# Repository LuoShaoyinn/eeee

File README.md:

# ESP32 Robot Controller

Four-wheel JGA25-2430-CE production controller for the carrier board. It uses active-low 20 kHz PWM, each motor's direction line, and the yellow FG speed output.

| Wheel | PWM | Direction | FG |
|---|---:|---:|---:|
| M1/front-left | GPIO23 | GPIO32 | GPIO36 |
| M2/front-right | GPIO21 | GPIO25 | GPIO39 |
| M3/rear-left | GPIO26 | GPIO27 | GPIO35 |
| M4/rear-right | GPIO19 | GPIO13 | GPIO34 |

The carrier supplies the required 3.3 V pull-ups for FG. FG is single-channel speed magnitude, not quadrature: it cannot prove direction. The firmware uses it for PI speed feedback and zero-speed confirmation before reversal; commanded DIR supplies the sign. Parameters are 18 FG pulses/output revolution, 620 RPM no-load, and 450 RPM rated-load. The wheel controller runs every 20 ms and updates its PCNT-derived RPM/PID feedback every 60 ms. The controller starts stopped, ramps duty, and stops after 500 ms without a valid command.

Chassis values: 190 mm wheel-center square and 23 mm wheel radius. The mirrored right-side mounts use inverted electrical direction by default (M2 and M4). Validate each wheel one at a time and correct `invert_direction` in `main/motor_control_main.c` for the actual Mecanum roller handedness/wiring. The FG source emits 9 pulses per motor-shaft revolution and the 9.6:1 gearbox yields 86.4 FG edges per output-shaft revolution. `encoder_pulses_per_output_rev` accepts fractional values for this reason.

`ROBOT_ENABLE_WIFI` in `main/motor_control_main.c` is `0` by default, so the
robot starts with its Wi-Fi radio and UDP listener disabled. The Cubie UART0
link is therefore the sole runtime control interface. Set the switch to `1`
to restore the retained AP/station and UDP control path; then copy
`main/wifi_credentials.h.example` to ignored local `main/wifi_credentials.h`.
An ESP32-WROOM-32 supports 2.4 GHz Wi-Fi only.

```sh
source /opt/esp-idf/export.sh
idf.py build
idf.py -p /dev/ttyUSB0 flash monitor
```

With the host connected to the ESP32 fallback AP:

```sh
python3 tools/keyboard_drive.py --host 192.168.4.1
```

UDP port `3333` accepts `drive FORWARD STRAFE TURN` with values from `-1.0` to `1.0`, `wheel MOTOR SPEED`, `stop`, `telemetry`, or `pid [KP KI]`. The PID query returns active gains; setting gains resets integrators immediately. The telemetry response contains per-wheel target, PCNT-derived RPM, latest FG edges, cumulative PCNT edges, duty, and reversal state. Subtract two `total` readings over a known interval to inspect hardware-counter edge rate directly.

Drive changes use a bounded PWM ramp. A regular `stop` coasts down at the configured deceleration rate. A direction reversal first ramps PWM to zero, waits for the FG signal to become quiet and observes the reversal dwell, then changes the direction line. A lost UDP command stream remains an immediate coast-to-stop safety action.

Minimal ESP-IDF application for an ESP32. The application prints `Hello, ESP32!` once per second over the default console UART.

## Hardware

The connected device was detected as:

- Chip: ESP32-D0WDQ6
- Revision: v1.1
- Features: Wi-Fi, Bluetooth, dual core
- Flash: 4 MB
- USB-UART port: `/dev/ttyUSB0`

The USB-UART bridge is a WCH CH340 (`1a86:7523`).

## Remote IMU debug

The carrier board's `J30` IMU header uses I2C. Connect JY61P `VCC` to `3V3`,
`GND` to `GND`, `SCL` to ESP32 `GPIO5`, and `SDA` to ESP32 `GPIO33`.
The firmware reads the module's default I2C address `0x50` at 100 kHz. Do not
also connect the JY61P UART pins for this integration.

From any device on the ESP32 Wi-Fi network, send UDP `imu` to port `3333`.
The reply reports the latest acceleration, angular rate, roll/pitch/yaw, frame
count, transaction-error count, and data age. A reply of `waiting for JY61P
I2C addr 0x50` indicates a wiring, supply, pull-up, or address/mode problem.

## S3 remote debug

S3 is a standard positional MG995 on GPIO17. At boot and after `stop`, PWM is
disabled, so a reset cannot move or hold a blocked linkage.
`s3 ANGLE` commands a slow one-degree-per-50-ms move over 0-180 degrees;
`s3 center` commands 60 degrees. `s3 release` stops PWM and releases holding
torque immediately. The MG995 has no angle readback: remove or align the horn
with the linkage at the intended center while unpowered before the first
installed test.

Send `s3` without an argument to inspect the commanded state. The reply shows
the most recently applied angle, target angle, 1,550-2,125 us pulse width,
50 Hz duty percentage, and the exact 16-bit LEDC duty count. After `s3
release`, the reported output duty is zero even though the last commanded angle
is retained for reference.

For unloaded endpoint calibration only, `s3 pulse PULSE_US` bypasses the angle
map and applies an immediate 1550-2125 us pulse at 50 Hz. Increase it in small
steps above 2000 us, and issue `s3 release` immediately if the servo buzzes,
heats, or reaches a hard stop. This command does not imply an angle.

Run `python3 tools/keyboard_drive.py --s3` on the host for a guarded manual
test: `A`/`D` adjust in 5-degree steps, `0` commands 0 degrees, `C` commands
60 degrees, and Space or Escape releases the servo.

Watch IMU telemetry over Wi-Fi with `python3 tools/keyboard_drive.py --imu`;
it keeps retrying until stopped with Ctrl-C, so it can be started before the
ESP32 powers on.

## Cubie UART debug and control

The carrier `JPI1` UART is ESP32 UART0 at 115200 baud, 8N1, with the 470 ohm
series resistors already fitted. Its connection is crossed: carrier
`PI_UART_TX_3V3` goes to Cubie RXD; carrier `PI_UART_RX_3V3` goes to Cubie TXD;
grounds join. Do not connect either 5 V or 3.3 V supply between boards.

Send one ASCII command per newline. UART accepts all production controls:
`state`, `imu`, `telemetry`, `drive F S T`, `twist VX_MPS VY_MPS WZ_RADPS`,
`wheel M SPEED`, `raw M DUTY`, `pid [KP KI]`, `s3 ANGLE`, `s3 center`,
`s3 release`, `ga25 DUTY`, and `stop`. Each command reply starts with `@ `.
For example, send `imu\n` to read the latest IMU data, or `s3 60\n` to move
S3 slowly to center. `s3 release\n` and `stop\n` release S3 immediately.

`state` is the compact control-loop snapshot: timestamp, IMU age/gyro/angle,
four wheel RPM/FG samples, and GA25 state. `twist` is the Cubie physical-unit
body command. It is conservatively limited to `+/-1.00 m/s` forward/strafe and
`+/-2.00 rad/s` yaw pending chassis calibration. The legacy normalized `drive`
command remains for bench tests.

Each chassis wheel has a hardware-PCNT speed PID loop. Startup ramps at 2.5%
duty per 20 ms to overcome static friction without an abrupt full-duty step.
When at least two wheels have valid encoder samples, a cross-wheel guard limits
any wheel running more than 10% ahead of the slowest commanded wheel ratio; the
lagging wheel retains its original PID target to recover. `telemetry` reports
this as `sync ACTIVE REFERENCE_RPM`.

The [Cubie C++ transport](cubie-robot/README.md) owns `/dev/ttyAS2` through
the enabled `robotd.service`. Its `robotctl` client communicates through a
local Unix socket rather than opening the serial port directly. `robotd`
refreshes active twists at 25 Hz, stops after 250 ms without client refreshes,
and relies on the ESP32's independent 500 ms watchdog as the second stop layer.

`raw M DUTY` is a single-JGA25 wheel wiring test which bypasses PCNT/encoder feedback
and PID. `M` is connector 1 through 4 and `DUTY` is -100 through 100. Refresh
the command within 500 ms while it should run; otherwise the firmware stops it.

The separate 6 V GA25-370 driving motor is controlled through the external
L298N, not `raw M DUTY`. Keep the L298N `ENA` jumper fitted. On the carrier's
`J40` header, GPIO12 (physical pin 3, 10 kOhm pulldown) drives L298N `IN1` and
GPIO16 (physical pin 1, 10 kOhm pulldown) drives L298N `IN2`. GPIO14 (physical
pin 2, no pulldown) is the single-channel GA25 encoder input. The PCB's old
`ENA`/`IN1`/`IN2` silkscreen labels therefore describe the physical traces, not
the new external L298N connection order. Never connect J40 pin 1 to L298N
`ENA`, and do not remove the L298N `ENA` jumper. The encoder must be a 3.3 V
safe signal before it reaches GPIO14.

Use `ga25 DUTY` for signed open-loop PWM. `ga25` reports the latest hardware
counter sample and cumulative encoder edges; no GA25 encoder PID is enabled
until its pulses-per-output-revolution is measured. Run `python3 tools/keyboard_drive.py --ga25 --host
192.168.19.137` for an interactive test; A/D change PWM by 5%, and Space/Esc
ramps to a stop.

### GA25 bench result

The external L298N and GA25-370 were verified with the above reassigned wiring.
Positive `ga25` duty produces a 20 kHz PWM waveform at the L298N motor output;
the motor-side average voltage is duty-scaled and includes the L298N bridge
drop, so it is lower than the 5 V supply. At 25% duty the measured average was
about 0.6 V, which was insufficient to reliably overcome static friction. The
motor started consistently at 80% duty.

The encoder on GPIO14 was counted by ESP32 PCNT hardware with a 10 us glitch
filter. With the mechanism free, five-second count windows measured:

| Command duty | Encoder edges | Window | Edge rate |
|---:|---:|---:|---:|
| 60% | 1,545 | 5.37 s | 288 edges/s |
| 80% | 2,633 | 5.34 s | 493 edges/s |

This confirms the encoder signal and the count rate scale with motor command.
It does not establish output RPM: measure encoder pulses per output revolution
before converting these counts into speed or enabling closed-loop GA25 control.
Always issue `ga25 0` or `stop` after a bench run; the command watchdog also
ramps GA25 to zero after 500 ms without refreshes.

### Collector recovery loop

The GA25 collector is disabled at ESP32 boot. `collector start` enables a
firmware-owned loop: it drives the collector reverse at 90%; if the GPIO14
encoder reports no edge for two seconds, it releases the L298N for 1.2 seconds,
then drives forward at 20% for exactly two output-shaft revolutions before
returning to reverse. This loop repeats until `collector stop`, `stop`, a
manual `ga25` command, or OTA update. A forward-clear phase taking more than
30 seconds enters a released `fault` state.

Before the first start, measure GPIO14 edges over a known number of output
shaft rotations and save the resulting edges-per-output-revolution value:

```sh
collector ppr EDGES_PER_OUTPUT_REV
collector start
collector
collector stop
```

The value is stored in ESP32 NVS and survives reboot. Without it, `collector
start` still runs reverse collection at 90%, but after a two-second stall it
releases and enters `fault`; it never estimates shaft revolutions from motor
time. Positive `ga25` duty is forward (`IN1` PWM) and negative duty is reverse
(`IN2` PWM).

## UART application updates

`partitions.csv` reserves two 1.875 MiB application slots. This enables updates
over the existing Cubie UART link after a one-time manual migration. The ESP32
ROM downloader cannot be entered from application code on this DevKit because
GPIO0 is only sampled during reset.

For the one-time migration, put the ESP32 in download mode with the physical
BOOT/EN buttons and flash the bootloader, partition table, and application in
one operation. Subsequent updates need no button press:

```sh
python3 tools/uart_ota_update.py build/esp32_hello_world.bin --port /dev/ttyAS2
```

The updater sends `ota SIZE CRC32` over UART0, writes the inactive slot, checks
the transferred image CRC32, marks that slot for the next boot, and reboots.
It stops the chassis, releases S3, and stops GA25 before accepting an image.
CRC32 protects against accidental serial corruption; it is not a signed or
authenticated update format, so only run the updater from the trusted Cubie.

## Environment

This project was built with ESP-IDF v6.0.2 on Arch Linux. Load the ESP-IDF toolchain before using `idf.py`:

```bash
source /opt/esp-idf/export.sh
```

## Build

Configure the target and build:

```bash
idf.py set-target esp32
idf.py build
```

The application binary is generated at `build/esp32_hello_world.bin`.

## Flash and monitor

Flash the connected board:

```bash
idf.py -p /dev/ttyUSB0 flash
```

Open the serial monitor at 115200 baud:

```bash
idf.py -p /dev/ttyUSB0 monitor
```

The monitor should show repeated `Hello, ESP32!` lines. Press `Ctrl-]` to exit.

## Project layout

- `CMakeLists.txt`: ESP-IDF project definition
- `main/hello_world_main.c`: application entry point
- `main/CMakeLists.txt`: component registration
- `sdkconfig.defaults`: shared default configuration
- `.gitignore`: generated ESP-IDF output exclusions

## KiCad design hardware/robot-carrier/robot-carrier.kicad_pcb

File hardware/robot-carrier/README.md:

# ESP32-WROOM-32 / Raspberry Pi 4B carrier board

This directory contains the first KiCad carrier-board sample for the mobile
robot. It is a placement and interface prototype, not yet a manufacturing
release. Power routing, thermal validation, and exact mechanical dimensions
must be reviewed before ordering a PCB.

## Project files

- `robot-carrier.kicad_pcb`: routed 60 mm x 73.5 mm two-sided board.
- `robot-carrier.kicad_sch`: authoritative electrical schematic.
- `robot-carrier.kicad_dru`: minimum widths for any added 5 V or battery tracks.
- `robot-carrier.kicad_pro`: KiCad project metadata.
- `RobotCarrier.kicad_sym`, `Custom.pretty/`, `sym-lib-table`, and
  `fp-lib-table`: project-local symbols and footprints.
- `carrier-architecture.md`: power tree, pin map, connector pinouts, and bring-up notes.
- `lcsc-selected-parts.md`: selected purchasable LCSC parts and remaining
  safety-critical sourcing decisions.

The board keeps the ESP32 DevKit on the carrier. The Raspberry Pi 4B is
physically separate and connects through `JPI1` using a jumper harness for
5 V, ground, and 3.3 V UART. The ESP32 socket is for the common 30-pin DevKit
V1 Type-C board, not a bare WROOM module footprint or the 38-pin DevKitC. It is
mounted on the front, component side up, using two 1x15 female Dupont headers.
The antenna points
toward the top power terminals and USB-C points toward J30/JPI1. The header
geometry is 25.40 mm between rows and 35.56 mm between the first and last pads
of each row. The measured board envelope is represented by a 28.5 mm by
50.42 mm silkscreen outline, with extra courtyard clearance. Dry-fit the exact
clone before soldering both socket strips because clone body and USB-shell
offsets can vary slightly.

The current JPI1 power pins may instead feed a short, 3 A-rated captive cable
ending in a USB-C male plug, so the Pi receives power through its USB-C input
rather than its GPIO header. Use a cable/plug assembly that correctly advertises
3 A on the USB-C CC connection; do not use an unverified VBUS/GND-only breakout.
UART remains on JPI1 pins 5-6. Do not power the Pi through USB-C and its 5 V GPIO
pins simultaneously.

## External power converter

The 24 V to 5 V converter is off-board. The selected converter is rated for
20 A maximum output to provide headroom; the expected total 5 V operating load
is below 10 A. Its input rating must include the 6S battery's 25.2 V
full-charge voltage. `J2` is its 24 V input terminal and `J3` is its 5 V output
terminal. The converter's 20 A capability does not mean the carrier normally
draws 20 A. Fit a provisional 10 A fuse or equivalent current-limited output
between the converter and J3; the protection setting must remain below both
J3's 16 A rating and the completed PCB copper rating.

The 6S Li-ion battery is used directly for the motor rail. Its advertised
24 V rating is nominal; the actual rail is approximately 18-25.2 V. The
previous 24 V stabilizer was removed to simplify the design. Add a 24 V
buck-boost stage only if the final motor test requires a constant voltage.
The default input wiring assumes the battery pack already includes correctly
rated protection. J1 connects directly to `VIN_PROTECTED`; this revision has
no battery fuse, eFuse, fuse-link footprint, or reverse-polarity stage. D1 is
the only on-board input protection: an axial 1.5KE33A TVS connected across the
battery rail beside J1. Verify battery polarity before connection.

The tested JGA25-2430-CE controller accepts direct 3.3 V PWM and direction
signals from the ESP32. The carrier does not use the previously considered
74AHCT125 level shifters. The motor connectors carry direct battery power;
the `*_3V3` names refer only to logic signals, never to motor power. Motor
signal traces share the carrier ground with the motor power return; the yellow
feedback input has a 10 k pull-up to the ESP32 DevKit's 3.3 V output. R9-R12
also pull the four active-low PWM inputs up to 3.3 V so an ESP32 reset produces
the stopped command rather than leaving the inputs floating.

The selected auxiliary motor is the low-load 6 V GA25-370. It is intentionally
operated from the 5 V rail through the physically external L298N module, so its
available terminal voltage, speed, and torque will be lower than when driven
directly at its nominal 6 V. Verify motor-terminal voltage, startup current,
loaded speed, and L298N temperature on the assembled system.

`J40` is a three-pin Dupont logic header for `ENA`, `IN1`, and `IN2`; `J41` is
a three-position screw terminal for motor 5 V, ground, and logic 5 V. The motor
connects to the L298N module's own output screw terminals. The module is not
galvanically isolated: its ground must join carrier ground. Remove both the
channel-A `ENA` jumper and the `5V_EN` jumper. Drive `ENA` from J40 pin 1 and
feed the module's 5 V logic terminal from J41 pin 3.

C5 provides one shared 100 nF bypass from the direct battery rail to ground for
the four nearby JGA motor connectors. C4 provides one shared 100 nF bypass from
+5 V to ground beside J41. These board capacitors shorten high-frequency
supply-current loops but do not replace C1/C3 bulk capacitance or the
battery-side TVS. For the brushed
GA25-370 itself, solder a separate non-polarized 100 nF ceramic capacitor
directly across the two motor terminals with the leads as short as possible.
Do not place a polarized capacitor across the L298N output terminals because
their polarity reverses with motor direction.

The GA25-370 encoder is not used. Its feedback wires remain insulated and
disconnected. All four M1-M4 encoder inputs are required and remain dedicated
to the four JGA25-2430-CE motors. The only otherwise unused exposed GPIOs are
GPIO0, GPIO2, and GPIO15, all of which are boot-strapping pins; there is no
unused safe GPIO pair for the GA25-370 quadrature encoder.

The external IMU connects at `J30` using I2C: GPIO5 is SCL and GPIO33 is SDA.
R5 and R6 provide optional 4.7 k pull-up footprints and are DNP by default
because the selected external modules provide their own I2C pull-ups. Fit them
only if the assembled bus lacks adequate pull-ups. Power the modules from the
ESP32 DevKit's 3.3 V output, not 5 V, so their pull-ups cannot expose the ESP32
to 5 V. Verify the exact VCC/GND/SCL/SDA order before making the harness.

The 5 V converter is specified for the battery input range. The motor rail is
not regulated, so confirm the motor's full-charge voltage tolerance and use a
hardware emergency stop for bring-up.

## Safety status

Before connecting a battery:

1. Confirm the assumed battery protection is suitable for the wiring,
   motor-stall current, and converter input. Populate D1 beside J1 with its
   cathode on `VIN_PROTECTED` and anode on `GND`. This revision intentionally
   has no reverse-polarity stage, so verify J1 polarity before every battery
   connection.
2. Wire the external buck as `J2 -> IN` and `OUT -> provisional 10 A fuse or
   equivalent current limit -> J3`, only after confirming its pinout against
   the purchased manufacturer's part.
3. Power the board without motors or servos and verify the battery rail and
   `+5V` at J3 and at the remote Pi harness.
4. The carrier and all attached devices are powered on together. The L298N
   channel remains disabled during ESP32 startup through R8's hardware `ENA`
   pull-down. R9-R12 hold the four active-low JGA25-2430-CE PWM inputs high
   while the ESP32 GPIOs are undriven during reset. These pull-ups do not stop
   an MCPWM peripheral that continues its last waveform during a CPU hang; use
   an independent watchdog or motor-power enable if that failure must stop the
   motors.
5. Add a hardware emergency-stop that removes motor and servo power.
6. Verify the Pi UART harness direction: ESP32 TX goes to Pi RX, and Pi TX
   goes to ESP32 RX. The Pi may flash the ESP32 through UART0 after the serial
   console and normal application are stopped and the ESP32 is manually put in
   download mode. Do not connect a DevKit USB-UART transmitter at the same time.

## KiCad checks

Run these commands from this directory:

```bash
kicad-cli sch erc robot-carrier.kicad_sch \
  --output erc-report.txt --severity-all
kicad-cli pcb drc robot-carrier.kicad_pcb \
  --output drc-report.txt
kicad-cli pcb render robot-carrier.kicad_pcb \
  --output robot-carrier-3d.png
kicad-cli pcb export gerbers robot-carrier.kicad_pcb \
  --output gerbers
```

The schematic is the authoritative electrical source and currently passes ERC.
Freerouting routed the logic signals. Its 0.20 mm power trees were subsequently
removed through KiCad's `pcbnew` API and replaced with a bottom-layer GND plane,
a front-layer `VIN_PROTECTED` plane on the left, and a front-layer +5 V plane on
the right. A 1.5 mm back-layer bridge connects the ESP32 5 V pad to the main 5 V
plane. R7 and R8 each use a short 0.5 mm track and dedicated via to the GND
plane. The final current capacity still depends on measured motor/servo current,
copper weight, neck-downs, ambient temperature, and permitted temperature rise;
use 2 oz outer copper for the intended high-current prototype.

This revision targets full hand assembly. R1-R4 and R7-R12 are supplied as 0805
parts on custom hand-solder pads (1.2 mm x 1.4 mm per pad). C4 and C5 are
through-hole ceramics on 5.08 mm pitch
with 2.4 mm pads. There are no small SMD capacitors to install. JLC/LCSC Basic
versus Extended assembly classification is therefore not a selection
constraint, although stock must still be rechecked before ordering.

For easiest assembly, solder R1-R4 and R7-R12 before installing the tall
connectors and electrolytic capacitors. Tin one resistor pad, reflow that end
while positioning the part with tweezers, then solder the other end. C4 and C5
are non-polarized; C1 and C3 are polarized and must follow the `+` marking.
Install D1 with its cathode toward `VIN_PROTECTED`. The PCB spacing is intended
to leave access to the resistor ends and to the underside of all through-hole
pads.

JESP1's body courtyard intentionally encloses R1-R4 and R7-R12: those low 0805
parts sit below the socketed DevKit. This produces ten deliberate courtyard
overlap errors in DRC. Solder and inspect the resistors first, and dry-fit the
actual socket/module combination to confirm more than 2 mm vertical clearance
above the finished resistor joints before accepting those ten errors.

The compact placement rotates components in the plane of the PCB rather than
standing axial parts on end. J10-J13 face the left edge, J20-J23 face the right
edge, and the battery, converter, and L298N power terminals occupy the top edge.
J30 and JPI1 occupy the bottom edge and act as a physical guard in front of the
front-mounted ESP32 USB connector. Their XY courtyard overlap with the DevKit
is intentional because the female sockets provide ample vertical separation,
but USB is not intended to be connected while the DevKit is installed. Use the
Raspberry Pi UART0 link for installed flashing and serial diagnostics. J40 and
D1 sit near the lower-left corner. D1 remains flat against the PCB for vibration
resistance; C1 and C3 use their normal upright radial mounting.

## Reference material versus selected parts

[实验材料说明.pdf](../../docs/实验材料说明.pdf) is the provided catalogue of
available example parts, not the carrier's authoritative BOM. In particular,
its 12 V motor example and LM2596 supply example are not the selected auxiliary
motor or 5 V converter. This carrier uses the 6 V GA25-370 at low load, the
pictured L298N module, and an external 24 V to 5 V converter rated for 20 A
maximum output. The Markdown files in this directory and `lcsc-bom.csv` define
the current design choices.

## Visual inspection and logic checks

Open the PCB in KiCad's PCB Editor:

```bash
pcbnew hardware/robot-carrier/robot-carrier.kicad_pcb
```

In PCB Editor:

1. Use the Appearance panel's **Nets** tab to show or hide a net. Right-click
   a net and choose **Highlight** to dim everything except that connection.
2. Turn on the ratsnest. The saved routed board currently has zero unconnected
   items; any ratsnest line therefore indicates a new or disturbed connection.
3. Use **Inspect -> Net Inspector** to verify the pads belonging to a net.
   For example, `M1_PWM_3V3` must contain ESP32 GPIO23 and motor connector J10
   pad 3; `M1_ENC` must contain GPIO36, J10 pad 5, and R1 pad 1.
4. Run **Inspect -> Design Rules Checker**. Shorts, clearance errors,
   wrong-net connections, and missing connections are not acceptable. The ten
   documented JESP1-to-resistor courtyard overlaps remain intentional.
5. Use **View -> 3D Viewer** to inspect board orientation, sockets, connector
   positions, and mounting-hole clearance. It does not verify electrical
   connectivity.

For a text netlist report:

```bash
kicad-cli pcb export ipcd356 \
  robot-carrier.kicad_pcb --output /tmp/robot-carrier.ipc356
```

After any schematic change, run ERC and use KiCad's **Update PCB from
Schematic** workflow. Refill all zones and re-run PCB DRC after every placement
or routing change.

## LCSC / JLC production workflow

LCSC PCBA currently requests an RS-274X Gerber archive, BOM, and pick-and-place
file. It supports both SMD and THT assembly, but availability and assembly
eligibility must be checked for every selected component at order time.

The production workflow for this project is:

1. Verify the board outline, layer count, copper thickness, minimum track
   width, and connector drill sizes against the current LCSC quotation page.
2. Select exact LCSC part numbers for all SMD resistors, capacitors,
   protection parts, and connectors.
3. Keep the Pi, ESP32 DevKit, and high-power converter modules as customer-
   supplied or hand-installed parts unless LCSC confirms the exact package and
   assembly service.
4. Export KiCad Gerbers, NC drill, BOM, and CPL/pick-and-place data.
5. Upload the package to LCSC and inspect its rendered component placement
   before paying for fabrication.

The LCSC PCBA service documentation lists Gerbers, BOM, and pick-and-place as
the required PCBA inputs and supports THT assembly. See
<https://www.lcsc.com/pcba> and
<https://www.lcsc.com/faqs/pcba/pcb-pcba-files-for-quotation>.

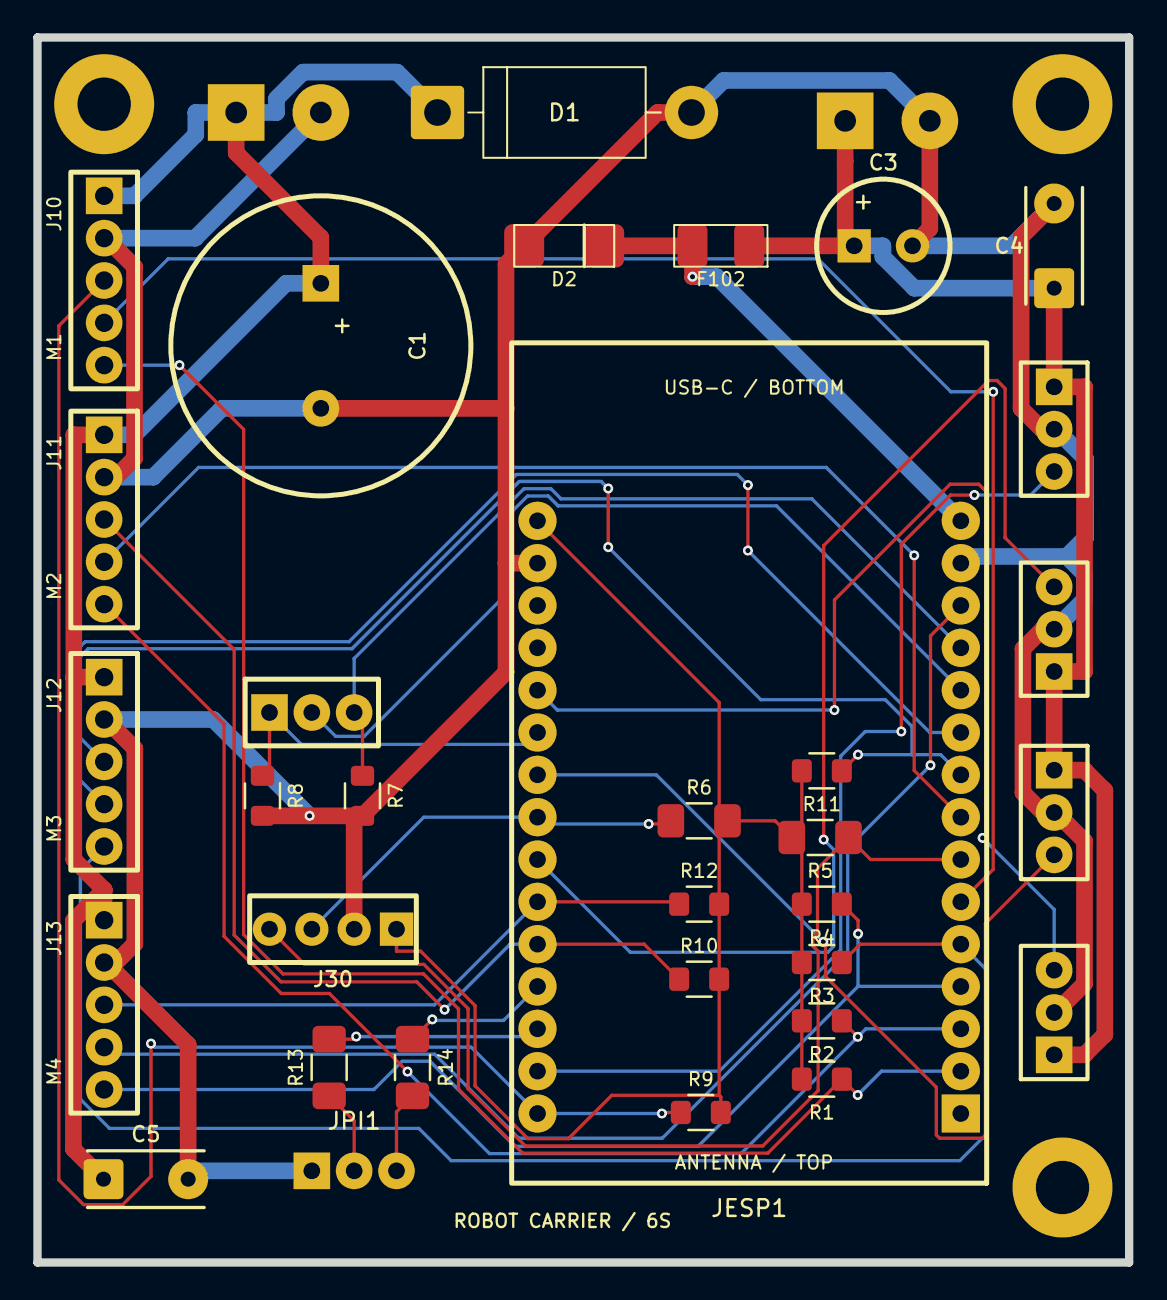
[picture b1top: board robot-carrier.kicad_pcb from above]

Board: 2 copper layers, 65.5 x 73.5 mm, 38 parts (0 on the bottom side), 30 nets.

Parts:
C1: HRK 2200uF 63V CD288, LCSC C2960335; CP_Radial_D18.0mm_P7.50mm
C3: 1000uF 16V, LCSC C51934166; CP_Radial_D8.0mm_P3.50mm
C4: 100nF 50V 5V shared, LCSC C84772; C_THT_P5.08_HAND
C5: 100nF 50V 24V shared, LCSC C84772; C_THT_P5.08_HAND
D1: 1.5KE33A, LCSC C18198472; D_DO-201AD_P15.24mm_Horizontal
D2: SMAJ5.0A; D_SMA
F102: PPTC 0.75A 6V; Fuse_1812_4532Metric
H1, H2, H3: M3; MountingHole_M3
J1: DB128L BAT IN, LCSC C500021; TERM_BLOCK_1X02
J3: DB128L 2P, LCSC C500021; TERM_BLOCK_1X02
J10: M1; MOTOR_5PIN
J11: M2; MOTOR_5PIN
J12: M3; MOTOR_5PIN
J13: M4; MOTOR_5PIN
J20: S1; SERVO_3PIN
J21: S2; SERVO_3PIN
J22: S3; SERVO_3PIN
J23: S4; SERVO_3PIN
J30: IMU I2C; UART_1X04
J40: GA25-370 L298N: ENA / IN1 / IN2; DUPONT_MALE_1X03
JESP1: ESP32 DEVKIT V1 30PIN TYPE-C; ESP32_DEVKIT_V1_30PIN_SOCKET
JPI1: RPI4B UART: GND / TX / RX; DUPONT_MALE_1X03
R1: 10k M1 ENC pull-up; R_0805_HAND
R2: 10k M2 ENC pull-up; R_0805_HAND
R3: 10k M3 ENC pull-up; R_0805_HAND
R4: 10k M4 ENC pull-up; R_0805_HAND
R5: 4.7k DNP I2C SDA pull-up; R_1206_HAND
R6: 4.7k DNP I2C SCL pull-up; R_1206_HAND
R7: 10k GA25 IN2 boot pull-down; R_0805_HAND
R8: 10k GA25 ENA safe pull-down; R_0805_HAND
R9: 10k M1 PWM safe pull-up; R_0805_HAND
R10: 10k M2 PWM safe pull-up; R_0805_HAND
R11: 10k M3 PWM safe pull-up; R_0805_HAND
R12: 10k M4 PWM safe pull-up; R_0805_HAND
R13: 470R Pi TX -> ESP RX; R_1206_HAND
R14: 470R ESP TX -> Pi RX; R_1206_HAND

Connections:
+3V3: J30.1, JESP1.30, R1.2, R2.2, R3.2, R4.2, R5.2, R6.2, R9.2, R10.2, R11.2, R12.2
+5V: C3.1, C4.1, F102.1, J3.1, J20.1, J21.1, J22.1, J23.1
+5V_ESP_PROTECTED: D2.1, F102.2, JESP1.15
ESP_UART_RX_3V3: JESP1.18, R13.2
ESP_UART_TX_3V3: JESP1.19, R14.1
GA25_ENA_PWM_3V3: J40.1, JESP1.25, R8.1
GA25_IN1_3V3: J40.2, JESP1.11
GA25_IN2_3V3: J40.3, JESP1.12, R7.1
GND: C1.2, C3.2, C4.2, C5.2, D1.2, D2.2, J1.2, J3.2, J10.2, J11.2, J12.2, J13.2, J20.2, J21.2, J22.2, J23.2, J30.2, JESP1.14, JESP1.29, JPI1.1, R7.2, R8.2
IMU_I2C_SCL_3V3: J30.3, JESP1.23, R6.1
IMU_I2C_SDA_3V3: J30.4, JESP1.7, R5.1
M1_DIR_3V3: J10.4, JESP1.6
M1_ENC: J10.5, JESP1.2, R1.1
M1_PWM_3V3: J10.3, JESP1.16, R9.1
M2_DIR_3V3: J11.4, JESP1.8
M2_ENC: J11.5, JESP1.3, R2.1
M2_PWM_3V3: J11.3, JESP1.20, R10.1
M3_DIR_3V3: J12.4, JESP1.10
M3_ENC: J12.5, JESP1.5, R3.1
M3_PWM_3V3: J12.3, JESP1.9, R11.1
M4_DIR_3V3: J13.4, JESP1.13
M4_ENC: J13.5, JESP1.4, R4.1
M4_PWM_3V3: J13.3, JESP1.21, R12.1
PI_UART_RX_3V3: JPI1.3, R14.2
PI_UART_TX_3V3: JPI1.2, R13.1
S1_PWM: J20.3, JESP1.17
S2_PWM: J21.3, JESP1.22
S3_PWM: J22.3, JESP1.24
S4_PWM: J23.3, JESP1.26
VIN_PROTECTED: C1.1, C5.1, D1.1, J1.1, J10.1, J11.1, J12.1, J13.1
